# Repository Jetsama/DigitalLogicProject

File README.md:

The Digital Logic Tool is used to help students visualize and use digital logic gates. Each logic gate becomes a physical object for the student to interconnect an experiement with.

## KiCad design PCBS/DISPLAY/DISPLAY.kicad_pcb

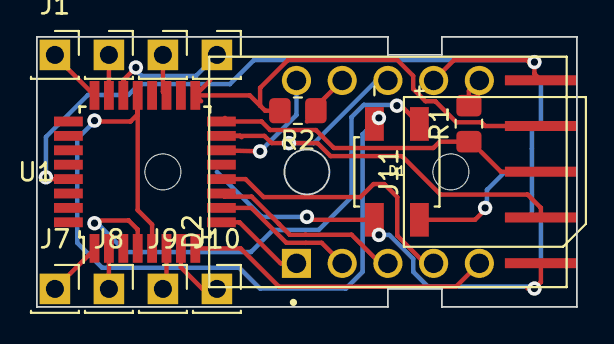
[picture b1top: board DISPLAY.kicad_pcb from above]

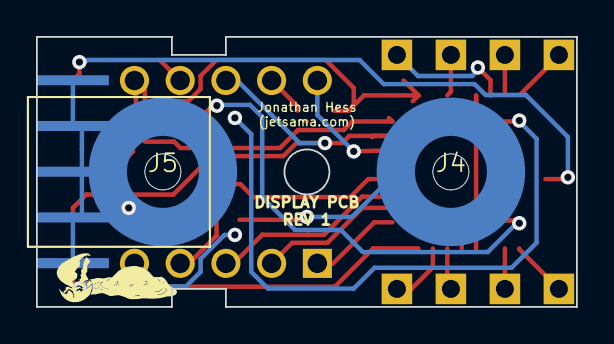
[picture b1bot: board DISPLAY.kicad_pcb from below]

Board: 2 copper layers, 30.0 x 15.0 mm, 16 parts (2 on the bottom side), 24 nets.

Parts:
D1: MB10F-13; DIOB_MB10F-13
D2: LTD-4708G; LED_LTD-4708G
J1, J2, J3, J6, J7, J8, J9, J10: Conn_01x01_Socket; PinSocket_1x01_P2.54mm_Vertical
J4, J5: 8mm-snap
J11: Conn_02x05_Odd_Even; Samtec_MECF-05-0_-NP-L-DV_2x05_P1.27mm_Edge
R1, R2: 300; R_0805_2012Metric_Pad1.20x1.40mm_HandSolder
U1: ATmega88PB-A; TQFP-32_7x7mm_P0.8mm

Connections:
DIGIT0: J11.5, R1.1, U1.16 (PB4)
DIGIT1: J11.7, R2.2, U1.17 (PB5)
GND: D1.3, U1.5 (GND), U1.21 (GND)
Input0: J1.1, U1.24 (PC1)
Input1: J2.1, U1.23 (PC0)
Input2: J3.1, U1.19 (PE2)
Input3: J6.1, U1.22 (PE3)
Input4: J7.1, U1.1 (PD3)
Input5: J8.1, U1.2 (PD4)
Input6: J9.1, U1.6 (PE1)
Input7: J10.1, U1.7 (XTAL1/PB6)
MOSI: D2.8, J11.3, U1.15 (PB3)
unnamed: D2.6, R1.2
unnamed: D2.9, R2.1
PW1: D1.2, J5.1 (PWR), J11.2, J11.4, J11.6, J11.8, J11.10
PW2: D1.4, J4.1 (PWR), J11.1
RST: D2.7, J11.9, U1.29 (~RESET/PC6)
SEG2: D2.3, U1.11 (PD7)
SEG3: D2.2, U1.10 (PD6)
SEG4: D2.1, U1.9 (PD5)
SEG5: D2.10, U1.14 (PB2)
SEG6: D2.4, U1.12 (PB0)
SEG7: D2.5, U1.8 (XTAL2/PB7)
VCC: D1.1, U1.4 (VCC)

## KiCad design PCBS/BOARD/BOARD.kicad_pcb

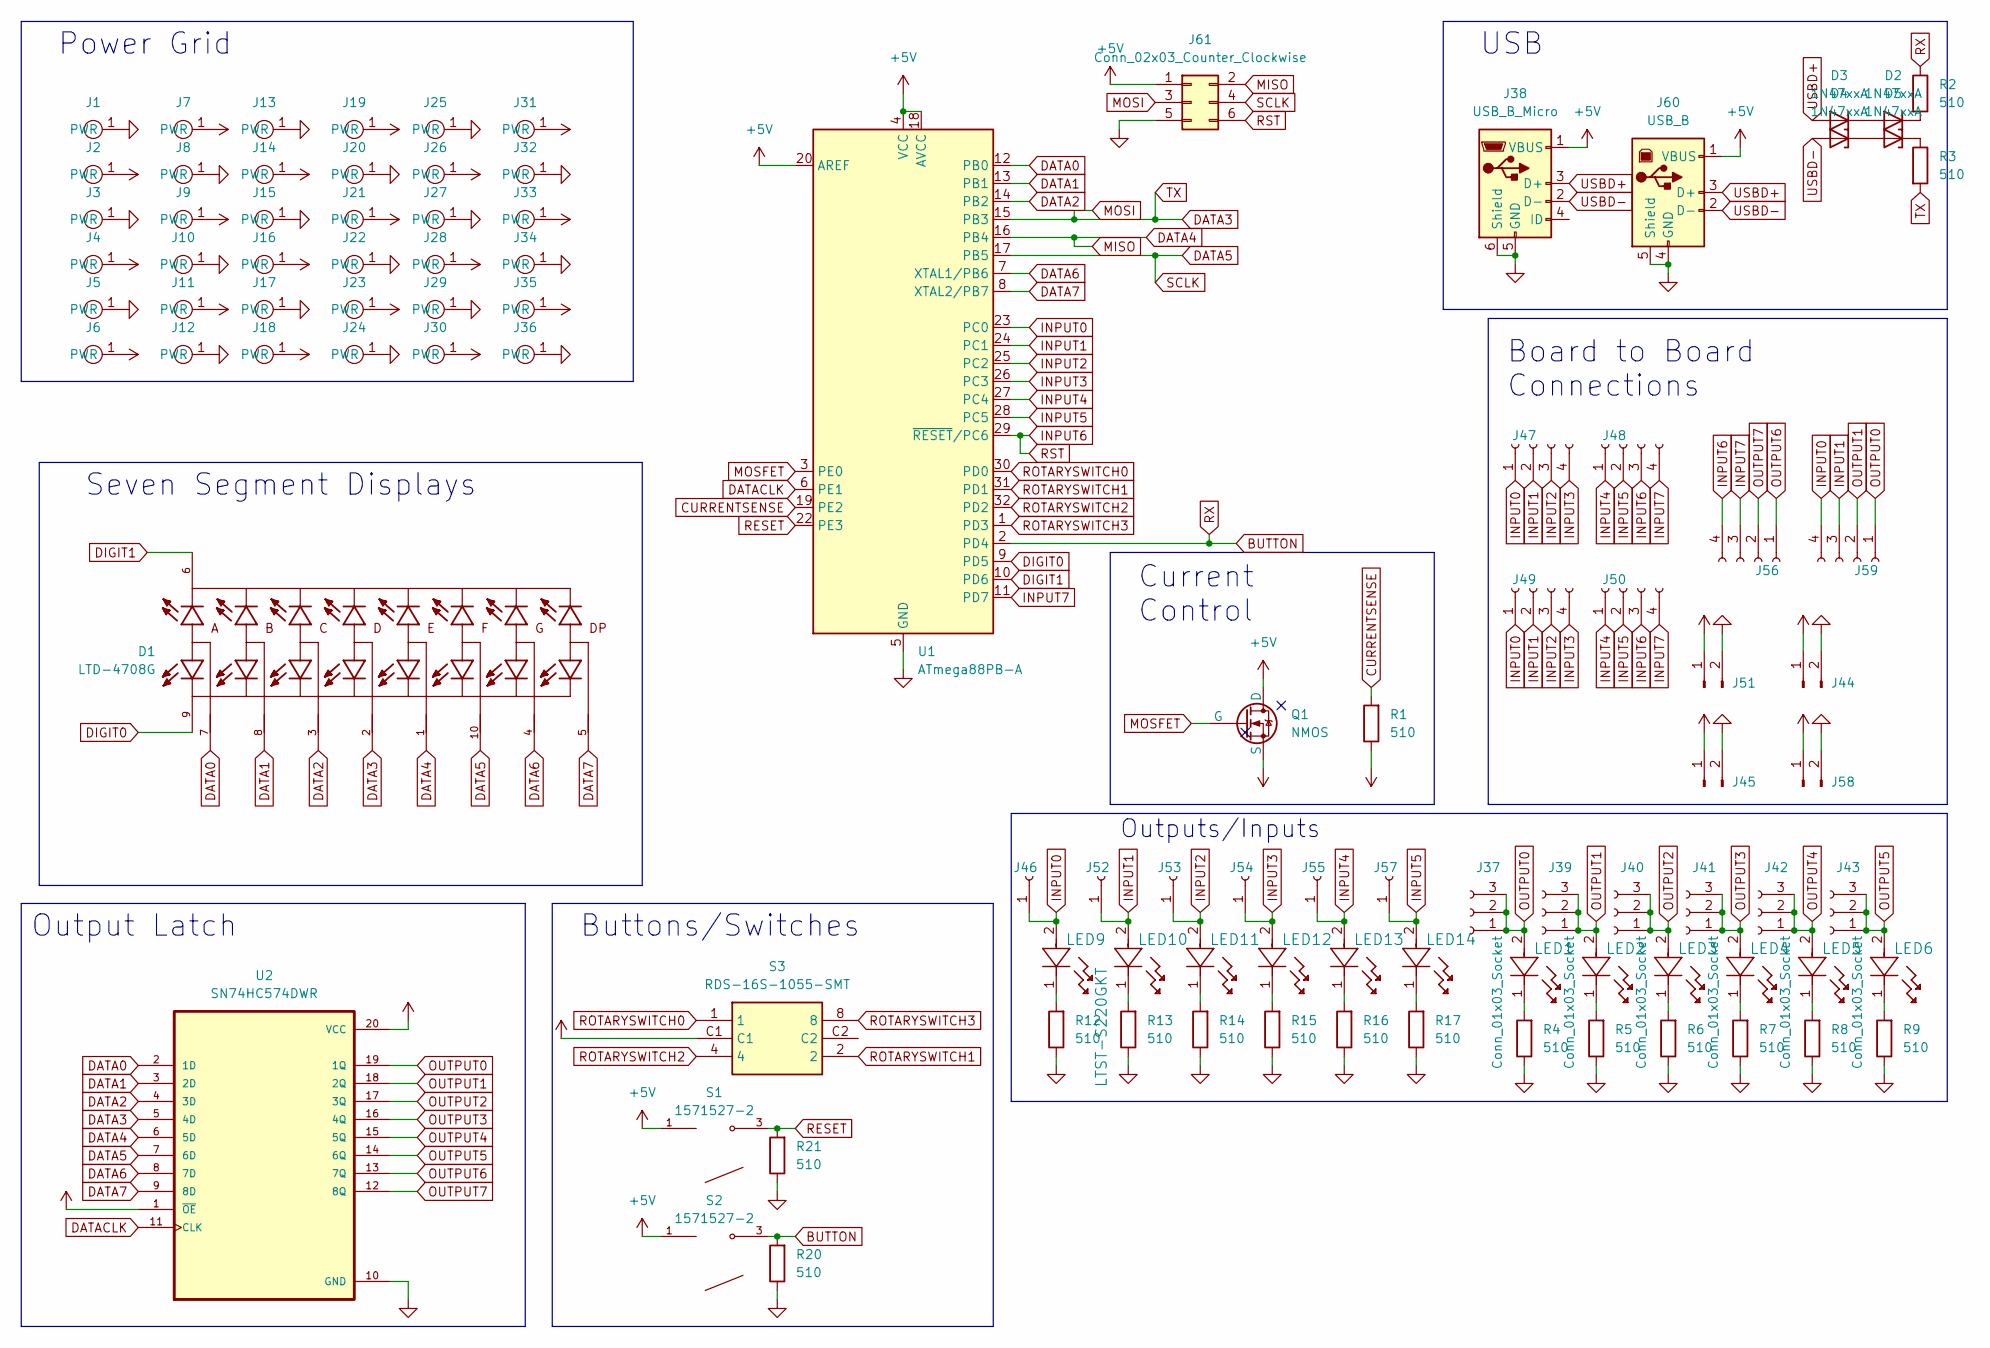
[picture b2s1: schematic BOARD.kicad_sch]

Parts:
D1: LTD-4708G; LED_LTD-4708G; PARTREV BNS-OD-C131/A4
D2, D3, D4, D5: 1N47xxA; D_DO-41_SOD81_P10.16mm_Horizontal
J1, J2, J3, J4, J5, J6, J7, J8, J9, J10, J11, J12, J13, J14, J15, J16, J17, J18, J19, J20, J21, J22, J23, J24, J25, J26, J27, J28, J29, J30, J31, J32, J33, J34, J35, J36: 8mm-snap
J37, J39, J40, J41, J42, J43: Conn_01x03_Socket; PinHeader_1x03_P2.54mm_Vertical
J38: USB_B_Micro; USB_Micro-B_Amphenol_10118194_Horizontal
J44, J45, J51, J58: Conn_01x02_Pin; PinHeader_1x02_P2.54mm_Horizontal
J46, J52, J53, J54, J55, J57: Conn_01x01_Socket; PinSocket_1x01_P2.54mm_Vertical
J47, J48, J49, J50, J56, J59: Conn_01x04_Socket; PinHeader_1x04_P2.54mm_Horizontal
J60: USB_B; USB_B_OST_USB-B1HSxx_Horizontal
J61: Conn_02x03_Counter_Clockwise; PinSocket_2x03_P2.54mm_Vertical
LED1, LED2, LED3, LED4, LED5, LED6, LED9, LED10, LED11, LED12, LED13, LED14: LTST-S220GKT; LED_LTST-S220GKT_LTO
Q1: NMOS; TO254P1041X444X1930-3
R1, R2, R3, R4, R5, R6, R7, R8, R9, R12, R13, R14, R15, R16, R17, R20, R21: 510; R_0805_2012Metric_Pad1.20x1.40mm_HandSolder
S1, S2: 1571527-2; SW_1571527-2; PARTREV V
S3: RDS-16S-1055-SMT; RDS16S1055SMT; Mouser Part Number 490-RDS-16S-1055-SMT
U1: ATmega88PB-A; TQFP-32_7x7mm_P0.8mm
U2: SN74HC574DWR; SOIC127P1030X265-20N

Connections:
+5V: J38.1 (VBUS), J60.1 (VBUS), J61.1, Q1.1 (D), S1.1, S2.1, U1.4 (VCC), U1.18 (AVCC), U1.20 (AREF)
BUTTON: R2.1, R20.2, S2.3, U1.2 (PD4)
CURRENTSENSE: R1.2, U1.19 (PE2)
DATA0: D1.7, U1.12 (PB0), U2.2 (1D)
DATA1: D1.8, U1.13 (PB1), U2.3 (2D)
DATA2: D1.3, U1.14 (PB2), U2.4 (3D)
DATA3: D1.2, J61.3, R3.2, U1.15 (PB3), U2.5 (4D)
DATA4: D1.1, J61.2, U1.16 (PB4), U2.6 (5D)
DATA5: D1.10, J61.4, U1.17 (PB5), U2.7 (6D)
DATA6: D1.4, U1.7 (XTAL1/PB6), U2.8 (7D)
DATA7: D1.5, U1.8 (XTAL2/PB7), U2.9 (8D)
DATACLK: U1.6 (PE1), U2.11 (CLK)
DIGIT0: D1.9, U1.9 (PD5)
DIGIT1: D1.6, U1.10 (PD6)
GND: J1.1 (PWR), J3.1 (PWR), J5.1 (PWR), J8.1 (PWR), J10.1 (PWR), J12.1 (PWR), J13.1 (PWR), J15.1 (PWR), J17.1 (PWR), J20.1 (PWR), J22.1 (PWR), J24.1 (PWR), J25.1 (PWR), J27.1 (PWR), J29.1 (PWR), J32.1 (PWR), J34.1 (PWR), J36.1 (PWR), J38.5 (GND), J38.6 (Shield), J44.2, J45.2, J51.2, J58.2, J60.4 (GND), J60.5 (Shield), J61.5, R4.1, R5.1, R6.1, R7.1, R8.1, R9.1, R12.1, R13.1, R14.1, R15.1, R16.1, R17.1, R20.1, R21.1, U1.5 (GND), U1.21 (GND), U2.10 (GND)
INPUT0: J46.1, J47.1, J49.1, J59.4, LED9.2, U1.23 (PC0)
INPUT1: J47.2, J49.2, J52.1, J59.3, LED10.2, U1.24 (PC1)
INPUT2: J47.3, J49.3, J53.1, LED11.2, U1.25 (PC2)
INPUT3: J47.4, J49.4, J54.1, LED12.2, U1.26 (PC3)
INPUT4: J48.1, J50.1, J55.1, LED13.2, U1.27 (PC4)
INPUT5: J48.2, J50.2, J57.1, LED14.2, U1.28 (PC5)
INPUT6: J48.3, J50.3, J56.4, J61.6, U1.29 (~RESET/PC6)
INPUT7: J48.4, J50.4, J56.3, U1.11 (PD7)
MOSFET: Q1.2 (G), U1.3 (PE0)
unnamed: D2.2 (A), D3.1 (K)
unnamed: D2.1 (K), R2.2
unnamed: D4.1 (K), D5.2 (A)
unnamed: D5.1 (K), R3.1
unnamed: LED1.1, R4.2
unnamed: LED2.1, R5.2
unnamed: LED3.1, R6.2
unnamed: LED4.1, R7.2
unnamed: LED5.1, R8.2
unnamed: LED6.1, R9.2
unnamed: LED9.1, R12.2
unnamed: LED10.1, R13.2
unnamed: LED11.1, R14.2
unnamed: LED12.1, R15.2
unnamed: LED13.1, R16.2
unnamed: LED14.1, R17.2
OUTPUT0: J37.1, J37.2, J37.3, J59.1, LED1.2, U2.19 (1Q)
OUTPUT1: J39.1, J39.2, J39.3, J59.2, LED2.2, U2.18 (2Q)
OUTPUT2: J40.1, J40.2, J40.3, LED3.2, U2.17 (3Q)
OUTPUT3: J41.1, J41.2, J41.3, LED4.2, U2.16 (4Q)
OUTPUT4: J42.1, J42.2, J42.3, LED5.2, U2.15 (5Q)
OUTPUT5: J43.1, J43.2, J43.3, LED6.2, U2.14 (6Q)
OUTPUT6: J56.1, U2.13 (7Q)
OUTPUT7: J56.2, U2.12 (8Q)
RESET: R21.2, S1.3, U1.22 (PE3)
ROTARYSWITCH0: S3.1, U1.30 (PD0)
ROTARYSWITCH1: S3.2, U1.31 (PD1)
ROTARYSWITCH2: S3.4, U1.32 (PD2)
ROTARYSWITCH3: S3.8, U1.1 (PD3)
USBD+: D3.2 (A), J38.3 (D+), J60.3 (D+)
USBD-: D4.2 (A), J38.2 (D-), J60.2 (D-)
VCC: J2.1 (PWR), J4.1 (PWR), J6.1 (PWR), J7.1 (PWR), J9.1 (PWR), J11.1 (PWR), J14.1 (PWR), J16.1 (PWR), J18.1 (PWR), J19.1 (PWR), J21.1 (PWR), J23.1 (PWR), J26.1 (PWR), J28.1 (PWR), J30.1 (PWR), J31.1 (PWR), J33.1 (PWR), J35.1 (PWR), J44.1, J45.1, J51.1, J58.1, Q1.3 (S), R1.1, S3.C1, U2.1 (~OE), U2.20 (VCC)

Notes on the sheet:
Seven Segment Displays
Board to Board Connections
Output Latch
USB
Buttons/Switches
Current Control
Outputs/Inputs
Power Grid

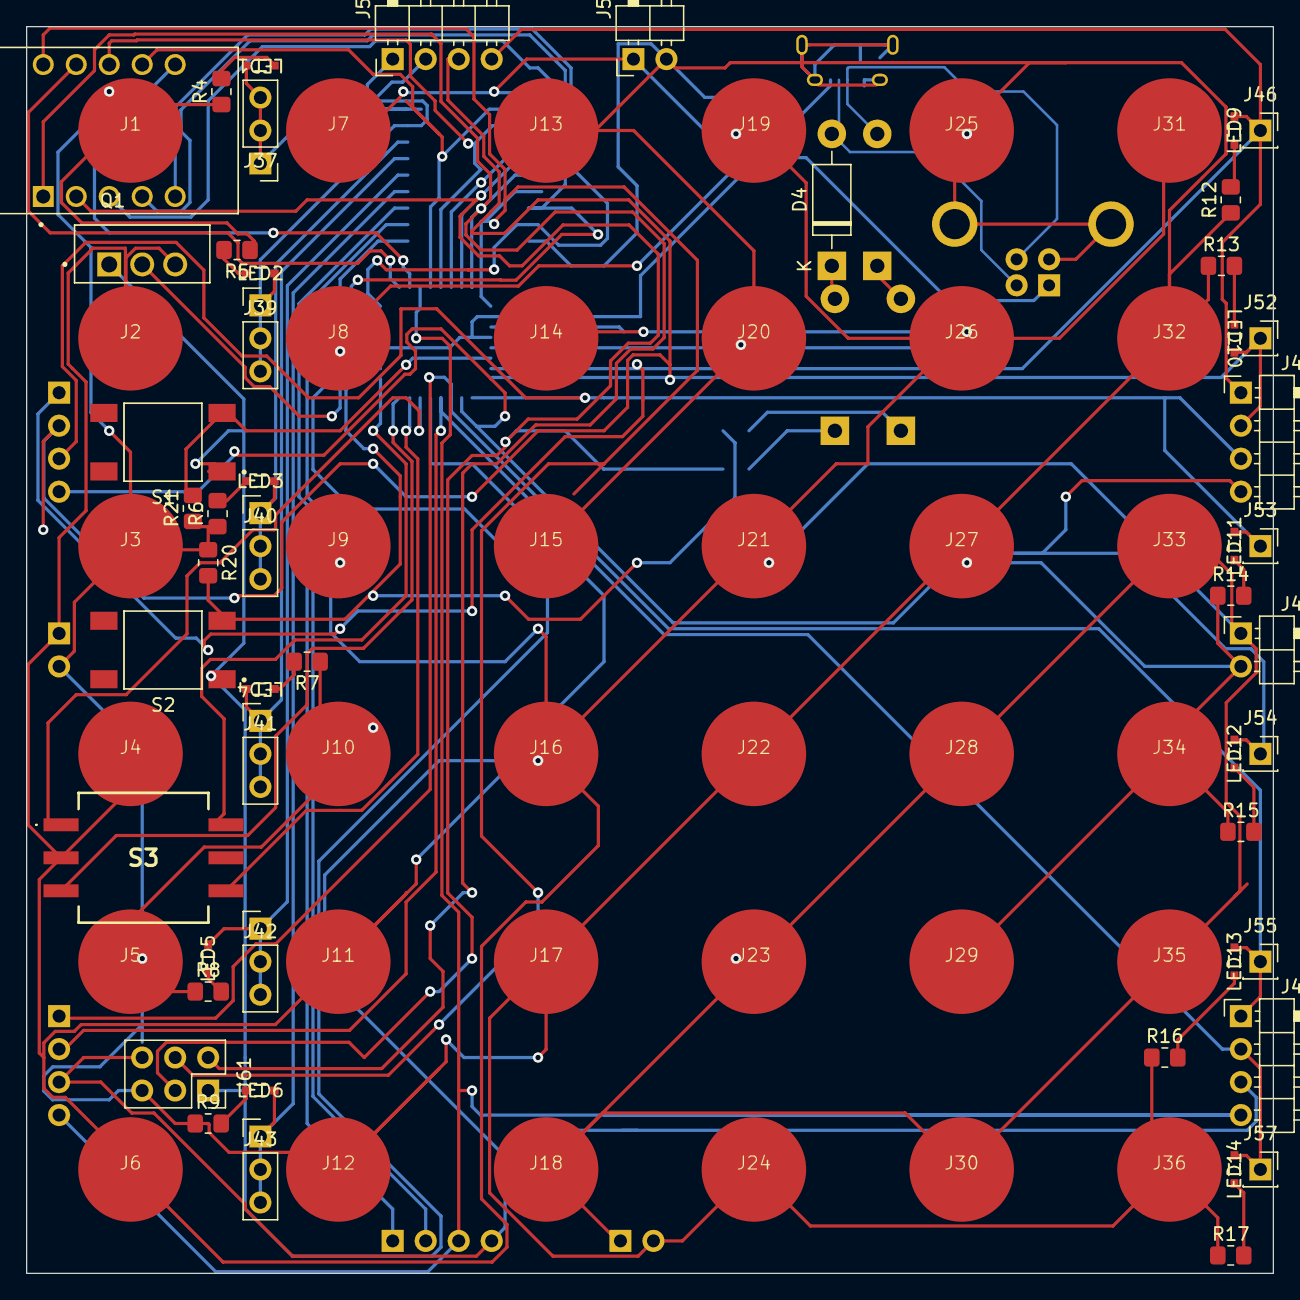
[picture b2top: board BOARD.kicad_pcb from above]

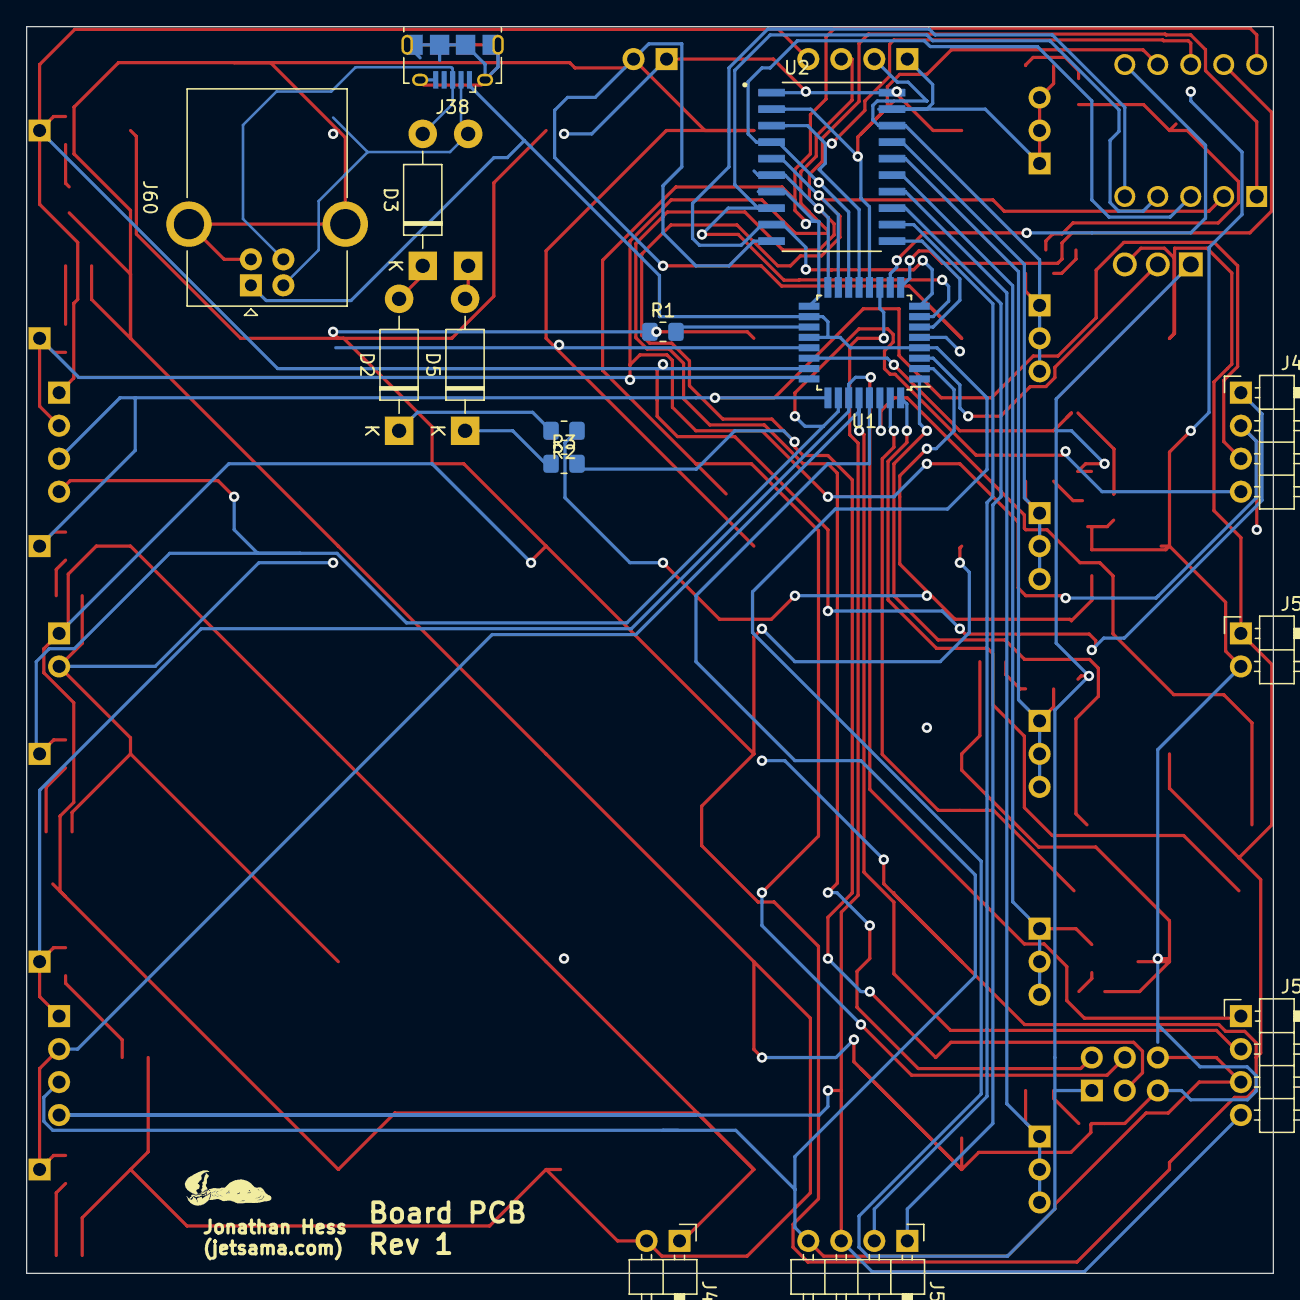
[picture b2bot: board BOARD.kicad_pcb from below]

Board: 2 copper layers, 96.0 x 96.0 mm, 101 parts (15 on the bottom side), 56 nets.

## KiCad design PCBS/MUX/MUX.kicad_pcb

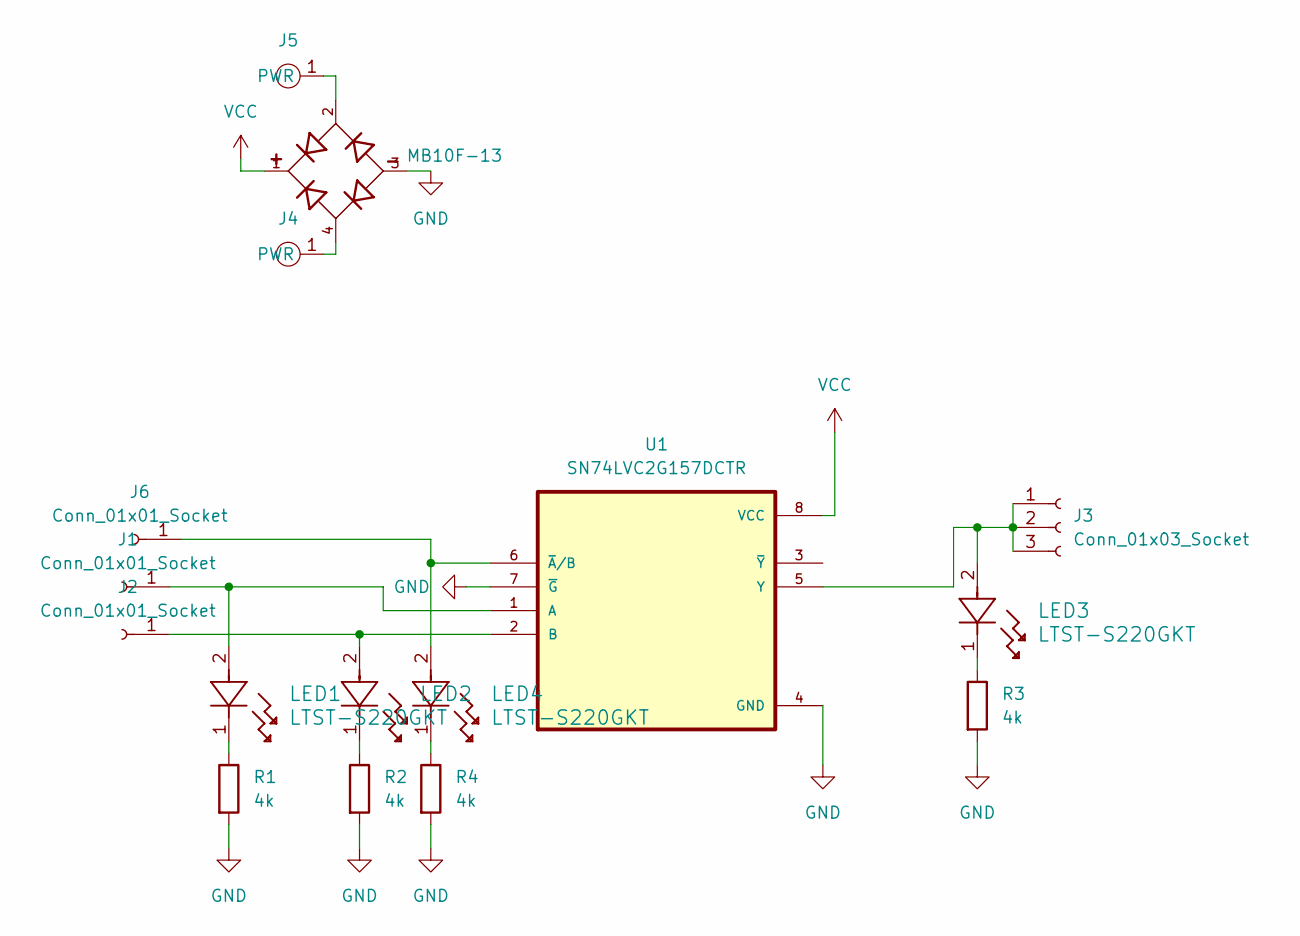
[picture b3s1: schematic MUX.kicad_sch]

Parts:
D1: MB10F-13; DIOB_MB10F-13; PARTREV 3 - 2
J1, J2, J6: Conn_01x01_Socket; PinSocket_1x01_P2.54mm_Vertical
J3: Conn_01x03_Socket; PinSocket_1x03_P2.54mm_Vertical
J4, J5: 8mm-snap
LED1, LED2, LED3, LED4: LTST-S220GKT; LED_LTST-S220GKT_LTO
R1, R2, R3, R4: 4k; R_0805_2012Metric_Pad1.20x1.40mm_HandSolder
U1: SN74LVC2G157DCTR; SOP65P400X130-8N

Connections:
GND: D1.3, R1.2, R2.2, R3.2, R4.2, U1.4 (GND), U1.7 (~G)
unnamed: J1.1, LED1.2, U1.1 (A)
unnamed: J2.1, LED2.2, U1.2 (B)
unnamed: J3.1, J3.2, J3.3, LED3.2, U1.5 (Y)
unnamed: D1.4, J4.1 (PWR)
unnamed: D1.2, J5.1 (PWR)
unnamed: J6.1, LED4.2, U1.6 (~A/B)
unnamed: LED1.1, R1.1
unnamed: LED2.1, R2.1
unnamed: LED3.1, R3.1
unnamed: LED4.1, R4.1
VCC: D1.1, U1.8 (VCC)

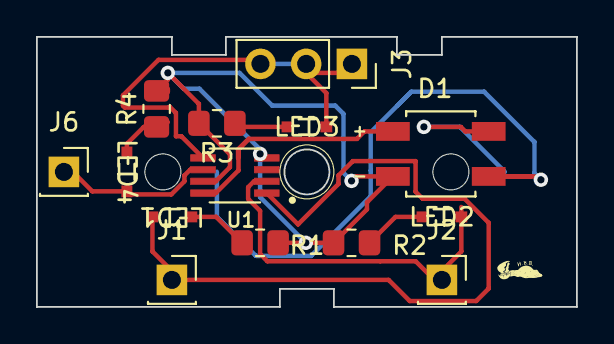
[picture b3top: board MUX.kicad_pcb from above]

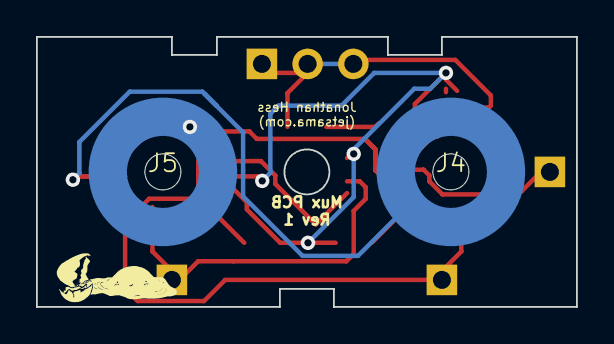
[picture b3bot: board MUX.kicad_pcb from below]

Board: 2 copper layers, 30.0 x 15.0 mm, 16 parts (2 on the bottom side), 12 nets.

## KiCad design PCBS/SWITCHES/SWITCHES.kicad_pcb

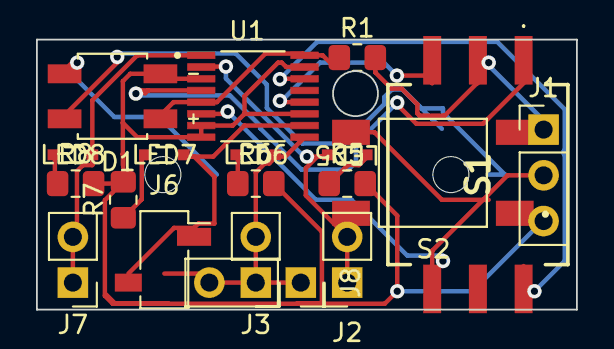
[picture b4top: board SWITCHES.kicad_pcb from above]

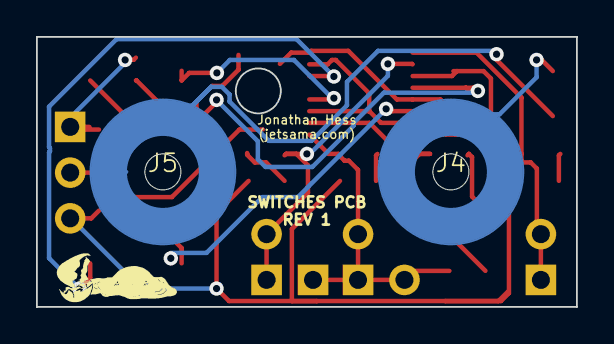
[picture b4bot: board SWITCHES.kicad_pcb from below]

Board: 2 copper layers, 30.0 x 15.0 mm, 21 parts (2 on the bottom side), 17 nets.

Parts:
D1: locked; DIOB_MB10F-13
J1: Conn_01x03_Pin; PinHeader_1x03_P2.54mm_Vertical
J2: Conn_01x02_Socket; PinSocket_1x02_P2.54mm_Vertical
J3, J7: Conn_01x02_Socket; PinHeader_1x02_P2.54mm_Vertical
J4, J5: 8mm-snap
J6: Conn_01x02_Socket; PinSocket_1x02_P2.54mm_Vertical_SMD_Pin1Right
J8: Conn_01x03_Socket; PinSocket_1x03_P2.54mm_Vertical
LED5, LED6, LED7, LED8: LTST-S220GKT; LED_LTST-S220GKT_LTO
R1: 10k; R_0805_2012Metric_Pad1.20x1.40mm_HandSolder
R5, R6, R7, R8: 4k; R_0805_2012Metric_Pad1.20x1.40mm_HandSolder
S1: RDS-16S-1055-SMT; RDS16S1055SMT
S2: 1571527-2; SW_1571527-2
U1: CD4043BPWR; SOP65P640X120-16N

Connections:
/DEBOUNCE0: S1.1, U1.4 (S1)
/DEBOUNCE1: J1.2, S1.2, S2.4, U1.6 (S2)
/DEBOUNCE2: S1.4, U1.12 (S3)
/DEBOUNCE3: S1.8, U1.14 (S4)
/OUTPUT0: J2.1, J2.2, LED5.2, S2.2, U1.2 (Q1)
/OUTPUT1: J3.1, J3.2, J8.1, J8.3, LED6.2, U1.9 (Q2)
/OUTPUT2: J6.1, J6.2, LED7.2, U1.10 (Q3)
/OUTPUT3: J7.1, J7.2, LED8.2, U1.1 (Q4)
/VCC_RES: J1.1, R1.2, S1.C1, S2.3
GND: D1.3, J1.3, R5.2, R6.2, R7.2, R8.2, S2.1, U1.3 (R1), U1.7 (R2), U1.8 (VSS), U1.11 (R3), U1.15 (R4)
unnamed: D1.4, J4.1 (PWR)
unnamed: D1.2, J5.1 (PWR)
unnamed: LED5.1, R5.1
unnamed: LED6.1, R6.1
unnamed: LED7.1, R7.1
unnamed: LED8.1, R8.1
VCC: D1.1, R1.1, U1.5 (ENABLE), U1.16 (VDD)

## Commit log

2023-09-16 LibrePCB start
2023-12-24 And gate start
2023-12-26 header pins and pcb start
2023-12-28 AND GATE passes DRC but with silk screen warnings
2023-12-28 Added mounting holes
2023-12-28 Added HBB logo
2023-12-29 Changed pins to 2.54mm from 1mm
2024-01-23 AND Gate Inventor 3D casing
2024-01-30 NOT gate PCB
2024-02-12 Added Mux PCB
2024-02-13 Input PCB Start
2024-02-13 Input PCB layout start
    4 Rocker Switches will not fit in 1x2 grid size but rotary switch might
2024-02-14 DRC pass on Inputs
    Need to find way to flip headers and add space inbetween headers. That or create way of shorting socket connections without PCB.
2024-02-14 Added Screw Hole
2024-02-14 move Logo
2024-02-14 Completed. SilkScreen changes necessary
    Uses one SMD right pin header socket for the rotary switch
2024-02-16 Finished input PCB and fixed mux and not
2024-02-16 Fixed mux
2024-02-16 Adding 3D models
2024-02-17 Created LICENSE for non commercial use
    With the goal to allow schools or individuals to create free of charge but remove commercial use.
2024-02-19 Added Board PCB
2024-03-07 Gate Rev 2 and Board Updates
2024-03-07 Honors poster
2024-03-14 Rev1 board/mux/switches/output
2024-03-15 Not Gate and And Gate models
2024-03-15 Gate Casings
2024-03-15 Mux Casing
2024-03-28 Updated gates models to 2mm hole
2024-04-11 Update screw hole and start board code
2024-05-09 Images and Poster
2024-05-11 honors PDF
